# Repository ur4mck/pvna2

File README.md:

# pvna2
Protable Vector Network Analyzer. Version 2

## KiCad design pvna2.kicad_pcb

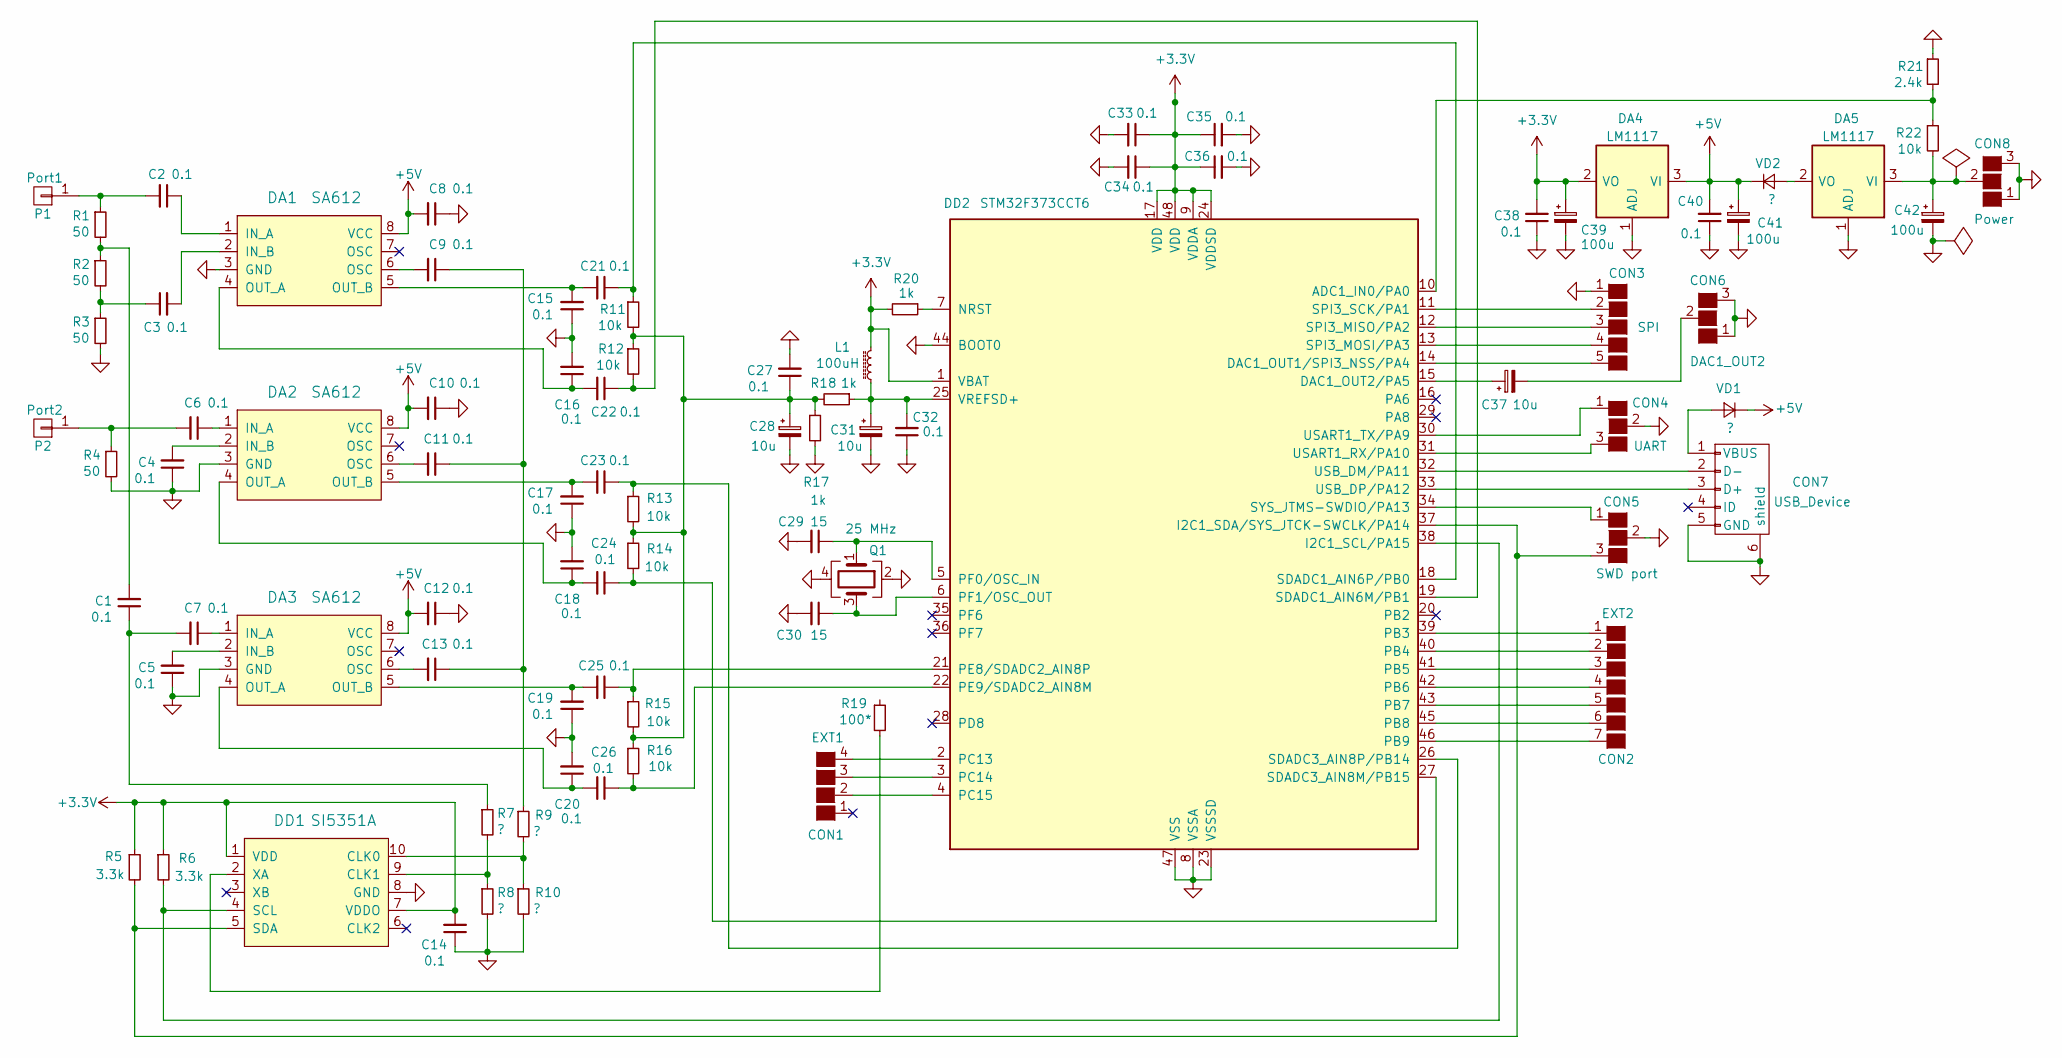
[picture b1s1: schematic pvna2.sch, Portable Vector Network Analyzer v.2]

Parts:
C1, C2, C3, C4, C5, C6, C7, C8, C9, C10, C11, C12, C13, C14, C15, C16, C17, C18, C19, C20, C21, C22, C23, C24, C25, C26, C27, C32, C33, C34, C35, C36, C38, C40: 0.1; C_0603
C28, C31, C37: 10u; CP_Tantalum_Case-A_EIA-3216-18_Reflow
C29, C30: 15; C_0603
C39, C41, C42: 100u; CP_Tantalum_Case-C_EIA-6032-28_Reflow
CON1: EXT1; GS4
CON2: EXT2; GS7
CON3: SPI; GS5
CON4: UART; GS3
CON5: SWD port; GS3
CON6: DAC1_OUT2; GS3
CON7: USB_Device; USB_Micro-B
CON8: Power; GS3
DA1, DA2, DA3: SA612; SOIC-8_3.9x4.9mm_Pitch1.27mm
DA4, DA5: LM1117; SOT-223
DD1: SI5351A; MSOP-10_3x3mm_Pitch0.5mm
DD2: STM32F373CCT6; LQFP-48_7x7mm_Pitch0.5mm
L1: 100uH; Inductor_1212
P1: Port1; SolderWirePad_single_SMD_5x10mm
P2: Port2; SolderWirePad_single_SMD_5x10mm
Q1: 25 MHz; Crystal_SMD_EuroQuartz_MJ-4pin_5.0x3.2mm_HandSoldering
R1, R2, R3, R4: 50; R_0603
R5, R6: 3.3k; R_0603
R7, R8, R9, R10: ?; R_0603
R11, R12, R13, R14, R15, R16, R22: 10k; R_0603
R17, R18, R20: 1k; R_0603
R19: 100*; R_0603
R21: 2.4k; R_0603
VD1, VD2: ?; D_SOD-123

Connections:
+3V3: C14.2, C33.1, C34.1, C35.1, C36.1, C38.2, C39.1, DA4.2 (VO), DA4.4 (VO), DD1.1 (VDD), DD1.7 (VDDO), DD2.1 (VBAT), DD2.9 (VDDA), DD2.17 (VDD), DD2.24 (VDDSD), DD2.48 (VDD), L1.2, R5.1, R6.1, R20.2
+5V: C8.2, C10.2, C12.2, C40.2, C41.1, DA1.8 (VCC), DA2.8 (VCC), DA3.8 (VCC), DA4.3 (VI), VD1.1 (K), VD2.1 (K)
GND: C4.1, C5.1, C8.1, C10.1, C12.1, C14.1, C15.1, C16.2, C17.1, C18.2, C19.1, C20.2, C27.2, C28.2, C29.2, C30.2, C31.2, C32.1, C33.2, C34.2, C35.2, C36.2, C38.1, C39.2, C40.1, C41.2, C42.2, CON3.1 (G1), CON4.2 (G2), CON5.2 (G2), CON6.1 (G1), CON6.3 (G3), CON7.5 (GND), CON7.6 (shield), CON8.1 (G1), CON8.3 (G3), DA1.3 (GND), DA2.3 (GND), DA3.3 (GND), DA4.1 (ADJ), DA5.1 (ADJ), DD1.8 (GND), DD2.8 (VSSA), DD2.23 (VSSSD), DD2.44 (BOOT0), DD2.47 (VSS), Q1.2, Q1.4, R3.2, R4.2, R8.2, R10.2, R17.2, R21.1
unnamed: C1.1, C7.2, R7.1
unnamed: C1.2, R1.2, R2.1
unnamed: C2.1, DA1.1 (IN_A)
unnamed: C2.2, P1.1, R1.1
unnamed: C3.1, R2.2, R3.1
unnamed: C3.2, DA1.2 (IN_B)
unnamed: C4.2, DA2.2 (IN_B)
unnamed: C5.2, DA3.2 (IN_B)
unnamed: C6.1, DA2.1 (IN_A)
unnamed: C6.2, P2.1, R4.1
unnamed: C7.1, DA3.1 (IN_A)
unnamed: C9.2, DA1.6 (OSC)
unnamed: C9.1, C11.1, C13.1, R9.1
unnamed: C11.2, DA2.6 (OSC)
unnamed: C13.2, DA3.6 (OSC)
unnamed: C15.2, C21.2, DA1.5 (OUT_B)
unnamed: C16.1, C22.2, DA1.4 (OUT_A)
unnamed: C17.2, C23.2, DA2.5 (OUT_B)
unnamed: C18.1, C24.2, DA2.4 (OUT_A)
unnamed: C19.2, C25.2, DA3.5 (OUT_B)
unnamed: C20.1, C26.2, DA3.4 (OUT_A)
unnamed: C21.1, DD2.18 (SDADC1_AIN6P/PB0), R11.1
unnamed: C22.1, DD2.19 (SDADC1_AIN6M/PB1), R12.2
unnamed: C23.1, DD2.26 (SDADC3_AIN8P/PB14), R13.1
unnamed: C24.1, DD2.27 (SDADC3_AIN8M/PB15), R14.2
unnamed: C25.1, DD2.21 (PE8/SDADC2_AIN8P), R15.1
unnamed: C26.1, DD2.22 (PE9/SDADC2_AIN8M), R16.2
unnamed: C27.1, C28.1, R11.2, R12.1, R13.2, R14.1, R15.2, R16.1, R17.1, R18.2
unnamed: C29.1, DD2.5 (PF0/OSC_IN), Q1.1
unnamed: C30.1, DD2.6 (PF1/OSC_OUT), Q1.3
unnamed: C31.1, C32.2, DD2.25 (VREFSD+), L1.1, R18.1
unnamed: C37.1, DD2.15 (DAC1_OUT2/PA5)
unnamed: C37.2, CON6.2 (G2)
unnamed: C42.1, CON8.2 (G2), DA5.3 (VI), R22.2
unnamed: CON1.2 (G2), DD2.4 (PC15)
unnamed: CON1.3 (G3), DD2.3 (PC14)
unnamed: CON1.4 (G4), DD2.2 (PC13)
unnamed: CON2.1 (G1), DD2.39 (PB3)
unnamed: CON2.2 (G2), DD2.40 (PB4)
unnamed: CON2.3 (G3), DD2.41 (PB5)
unnamed: CON2.4 (G4), DD2.42 (PB6)
unnamed: CON2.5 (G5), DD2.43 (PB7)
unnamed: CON2.6 (G6), DD2.45 (PB8)
unnamed: CON2.7 (G7), DD2.46 (PB9)
unnamed: CON3.2 (G2), DD2.11 (SPI3_SCK/PA1)
unnamed: CON3.3 (G3), DD2.12 (SPI3_MISO/PA2)
unnamed: CON3.4 (G4), DD2.13 (SPI3_MOSI/PA3)
unnamed: CON3.5 (G5), DD2.14 (DAC1_OUT1/SPI3_NSS/PA4)
unnamed: CON4.1 (G1), DD2.30 (USART1_TX/PA9)
unnamed: CON4.3 (G3), DD2.31 (USART1_RX/PA10)
unnamed: CON5.1 (G1), DD2.34 (SYS_JTMS-SWDIO/PA13)
unnamed: CON5.3 (G3), DD1.5 (SDA), DD2.37 (I2C1_SDA/SYS_JTCK-SWCLK/PA14), R5.2
unnamed: CON7.1 (VBUS), VD1.2 (A)
unnamed: CON7.2 (D-), DD2.32 (USB_DM/PA11)
unnamed: CON7.3 (D+), DD2.33 (USB_DP/PA12)
unnamed: DA5.2 (VO), DA5.4 (VO), VD2.2 (A)
unnamed: DD1.2 (XA), R19.2
unnamed: DD1.4 (SCL), DD2.38 (I2C1_SCL/PA15), R6.2
unnamed: DD1.9 (CLK1), R7.2, R8.1
unnamed: DD1.10 (CLK0), R9.2, R10.1
unnamed: DD2.7 (NRST), R20.1
unnamed: DD2.10 (ADC1_IN0/PA0), R21.2, R22.1

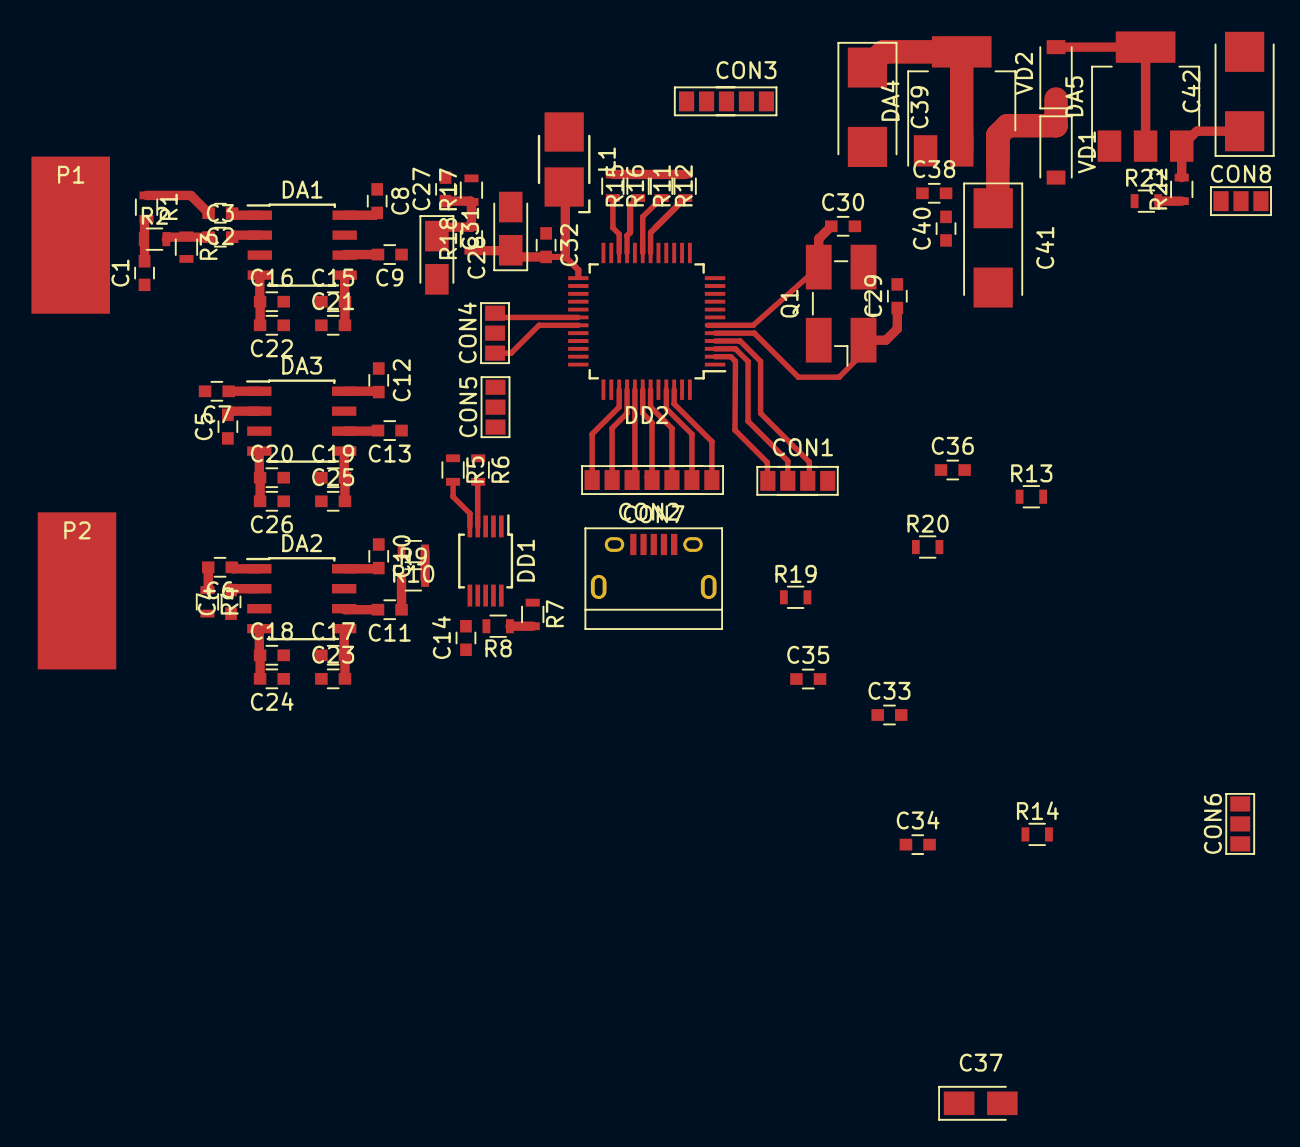
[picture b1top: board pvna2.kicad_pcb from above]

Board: 2 copper layers, 85 parts (0 on the bottom side), 65 nets.

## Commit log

2017-04-24 Adding files
